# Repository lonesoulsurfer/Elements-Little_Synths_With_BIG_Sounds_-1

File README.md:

# Elements: Little Synths With BIG Sounds #1

Elements is a small analogue synth. It has a pulse-width-modulated (PWM) oscillator and a resonant low-pass filter. It is number 1 in my "Little synths with BIG sounds" series.

## Build guide and video

- Step-by-step build guide on Instructables: [Elements - Little Synths With Big Sounds #1](https://www.instructables.com/Elements-Little-Synths-With-Big-Sounds-1/)
- Video on YouTube: [Elements](https://www.youtube.com/watch?v=f492427Ovs0)

## Features

- PWM oscillator with a "growling" sound, through a resonant low-pass filter
- Control the sound with 2 light-dependent resistors (LDRs), or with LEDs through 2 vactrols
- Knobs for cutoff, speed, modulation and resonance
- CV and gate outputs, to connect a sequencer or other synths
- The front panel is a PCB that fits over the main board
- No case and no complex power supply, to keep the build easy

## What you need

- All parts are in the parts list ([PDF](Parts%20List/Elements%20-%20Parts%20List%20-%20Excel.pdf) or Excel).
- The schematic is [schematic.png](schematic.png).
- The Gerber files for the PCB and the front panel are in [Gerber Files](Gerber%20Files/). You can send them to a PCB maker.

## Build it

The Instructables guide shows each step, with photos. In short:

1. Send the Gerber files to a PCB maker.
2. Get the parts in the parts list.
3. Solder the parts to the PCB.
4. Attach the front panel PCB.
5. Connect the power and test the synth.

## Files in this repository

| Folder or file | Contents |
|----------------|----------|
| `Eagle Files/` | Eagle files for the PCB |
| `Gerber Files/` | Gerber files for the PCB and the front panel, ready to order |
| `Parts List/` | Parts list (PDF and Excel) |
| `schematic.png` | Schematic |

## Support

Do you like this project? You can support my work on [GitHub Sponsors](https://github.com/sponsors/lonesoulsurfer).

## Licence

This project uses the [CERN Open Hardware Licence v2, Strongly Reciprocal](LICENSE) (CERN-OHL-S-2.0). Copyright (c) 2025 Marcus (lonesoulsurfer).

You can make, change and sell boards from these files. If you share or sell a changed design, you must also share the changed design files under the same licence.

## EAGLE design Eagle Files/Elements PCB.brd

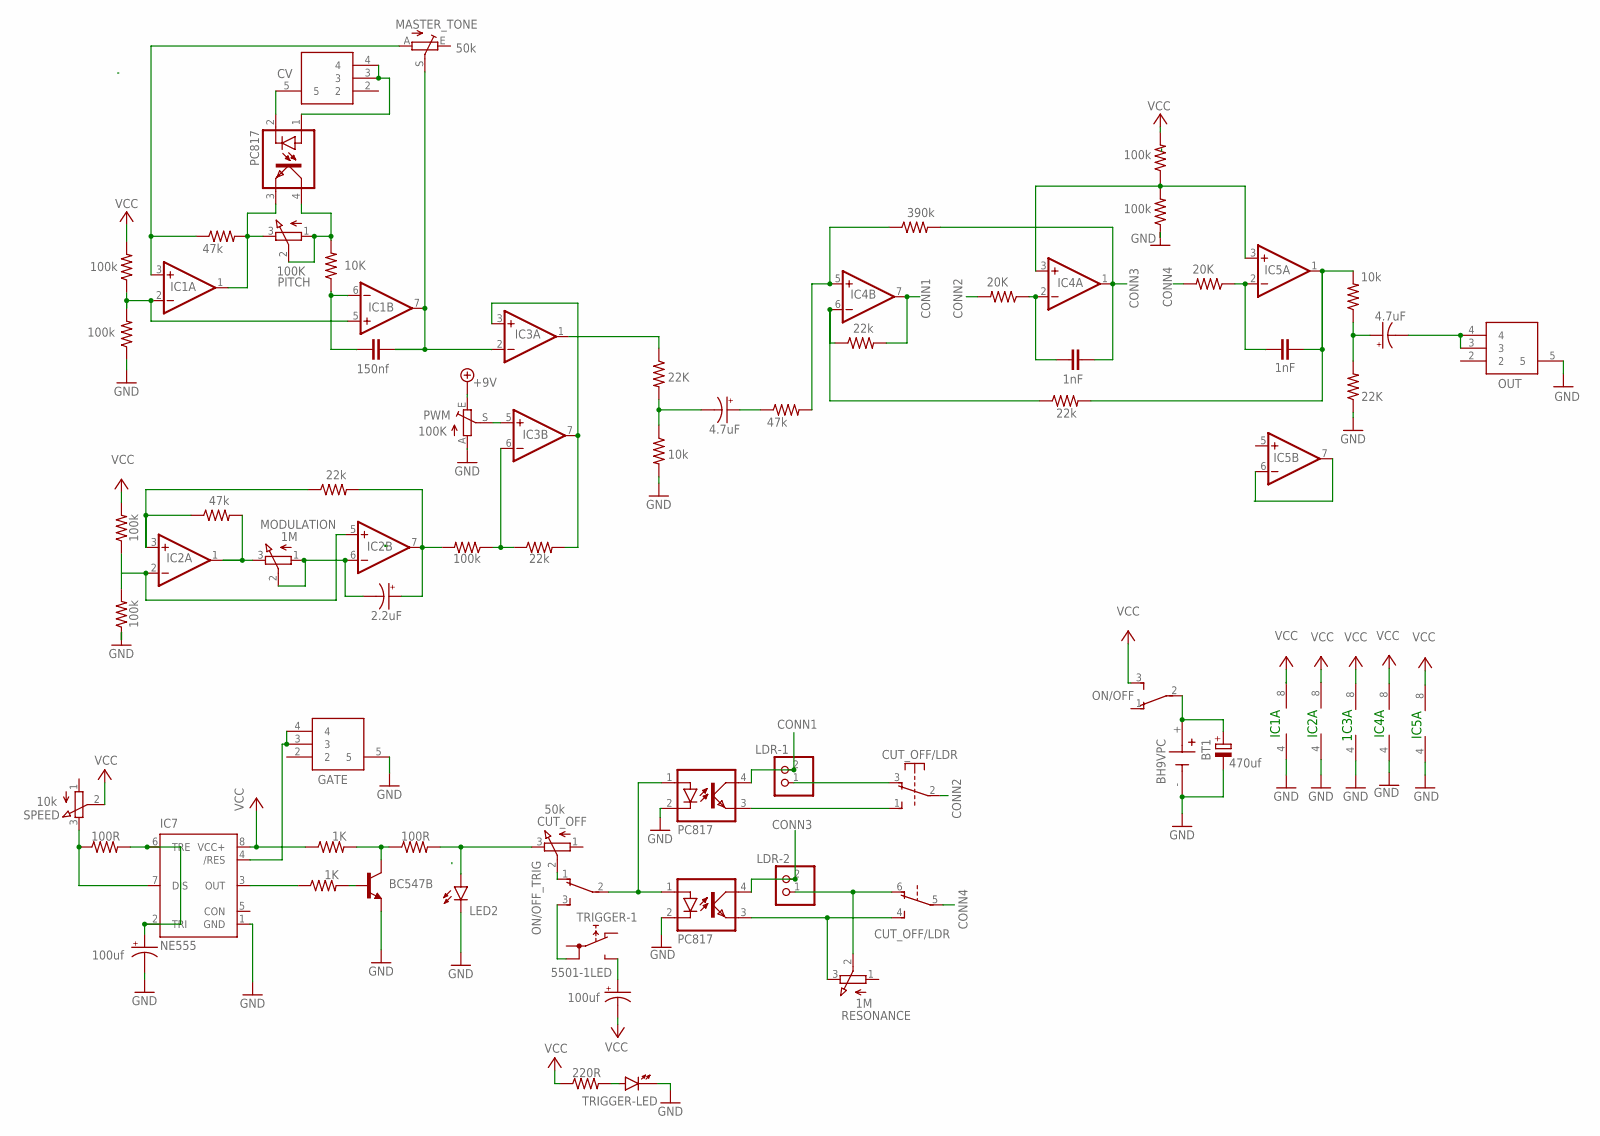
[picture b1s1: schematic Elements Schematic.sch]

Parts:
BT1: BH9VPC; BAT_BH9VPC
C1: 150nf; C050-024X044
C2: 2.2uF; E2,5-5
C3, C6: 4.7uF; E2,5-5
C4, C5: 1nF; C050-024X044
C7, C11: 100uf; E2,5-5
C8: 470uf; E3,5-8
CUT_OFF: 50k; EVUF
CUT_OFF/LDR: SWITCH-6PIN
CV: PJ-320A; PJ320A
GATE: PJ-320A; PJ320A
IC1, IC2, IC3, IC4, IC5: LM358N; DIL08
IC7: NE555; DIL-08
LDR-1, LDR-2: PINHD-1X2; 1X02
LED2: LED3MM
MASTER_TONE: 50k; B25P
MODULATION: 1M; EVUF
OK1, OK2, OK3: PC817; DIL04
ON/OFF: TL36PO; TL3XPO
ON/OFF_TRIG: TL36PO; TL3XPO
OUT: PJ-320A; PJ320A
PITCH: 100K; EVUF
PWM: 100K; B25P
Q1: BC547B; TO92
R1, R2, R3, R4, R7, R15, R19: 100k; 0207/10
R5, R12, R16: 47k; 0207/10
R6, R20: 20K; 0207/10
R8, R13, R18, R21: 22k; 0207/10
R9, R10: 10k; 0207/10
R11, R17: 22K; 0207/10
R14: 390k; 0207/10
R22: 10K; 0207/10
R23: 220R; 0207/10
R38, R40: 100R; 0207/10
R39, R41: 1K; 0207/10
RESONANCE: 1M; EVUF
SPEED: 10k; EVUF
TRIGGER: 5501-1LED

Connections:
CONN1: IC4.7 (OUT), LDR-1.2, OK1.4 (COL), R13.2
CONN2: CUT_OFF/LDR.2, R6.2
CONN3: C4.2, IC4.1 (OUT), LDR-2.2, OK3.4 (COL), R14.2
CONN4: CUT_OFF/LDR.5, R20.2
GND: BT1.-, C8.-, C11.-, GATE.5, IC1.4 (V-), IC2.4 (V-), IC3.4 (V-), IC4.4 (V-), IC5.4 (V-), IC7.1 (GND), LED2.K (C), OK1.2 (C), OK3.2 (C), OUT.5, PWM.A, Q1.1 (E), R2.1, R3.1, R10.2, R17.1, R19.1, TRIGGER.- (K)
unnamed: IC1.3 (+IN), MASTER_TONE.A, R5.1
unnamed: C1.1, IC1.6 (-IN), R22.1
unnamed: IC1.2 (-IN), IC1.5 (+IN), R1.1, R2.2
unnamed: C1.2, IC1.7 (OUT), IC3.2 (-IN), MASTER_TONE.S
unnamed: CUT_OFF.2 (S), ON/OFF_TRIG.1 (O)
unnamed: IC2.2 (-IN), IC2.5 (+IN), R3.2, R4.1
unnamed: IC2.3 (+IN), R16.1, R18.1
unnamed: IC2.1 (OUT), MODULATION.3 (E), R16.2
unnamed: C2.-, IC2.6 (-IN), MODULATION.1 (A), MODULATION.2 (S)
unnamed: C2.+, IC2.7 (OUT), R7.2, R18.2
unnamed: IC3.6 (-IN), R7.1, R8.1
unnamed: IC3.3 (+IN), IC3.7 (OUT), R8.2
unnamed: IC3.5 (+IN), PWM.S
unnamed: IC3.1 (OUT), R11.1
unnamed: C6.+, R9.1, R17.2
unnamed: C3.+, R12.1
unnamed: IC4.5 (+IN), R12.2, R14.1
unnamed: IC4.6 (-IN), R13.1, R21.1
unnamed: C6.-, OUT.3, OUT.4
unnamed: C5.2, IC5.1 (OUT), R9.2, R21.2
unnamed: C4.1, IC4.2 (-IN), R6.1
unnamed: IC4.3 (+IN), IC5.3 (+IN), R15.1, R19.2
unnamed: C3.-, R10.1, R11.2
unnamed: C5.1, IC5.2 (-IN), R20.1
unnamed: OK2.4 (COL), PITCH.1 (A), PITCH.2 (S), R22.2
unnamed: IC5.6 (-IN), IC5.7 (OUT)
unnamed: CV.5, OK2.2 (C)
unnamed: CV.3, CV.4, OK2.1 (A)
unnamed: ON/OFF_TRIG.3 (S), TRIGGER.1B
unnamed: C7.+, TRIGGER.NO
unnamed: R23.2, TRIGGER.+ (A)
unnamed: OK1.1 (A), OK3.1 (A), ON/OFF_TRIG.2
unnamed: GATE.3, GATE.4, IC7.4 (/RES)
unnamed: BT1.+, C8.+, ON/OFF.2
unnamed: IC1.1 (OUT), OK2.3 (EMIT), PITCH.3 (E), R5.2
unnamed: CUT_OFF.3 (E), LED2.A, R40.2
unnamed: CUT_OFF/LDR.3 (O), LDR-1.1
unnamed: CUT_OFF/LDR.1 (S), OK1.3 (EMIT)
unnamed: CUT_OFF/LDR.6 (O), LDR-2.1, RESONANCE.2 (S)
unnamed: CUT_OFF/LDR.4 (S), OK3.3 (EMIT), RESONANCE.3 (E)
unnamed: C11.+, IC7.2 (TRI), IC7.6 (TRE), R38.2
unnamed: IC7.7 (DIS), R38.1, SPEED.3 (E)
unnamed: Q1.3 (C), R40.1, R41.2
unnamed: IC7.3 (OUT), R39.1
unnamed: Q1.2 (B), R39.2
VCC: C7.-, IC1.8 (V+), IC2.8 (V+), IC3.8 (V+), IC4.8 (V+), IC5.8 (V+), IC7.8 (VCC+), ON/OFF.3 (S), PWM.E, R1.2, R4.2, R15.2, R23.1, R41.1, SPEED.2 (S)

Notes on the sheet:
IC1A
1C3A
IC2A
IC4A
IC5A

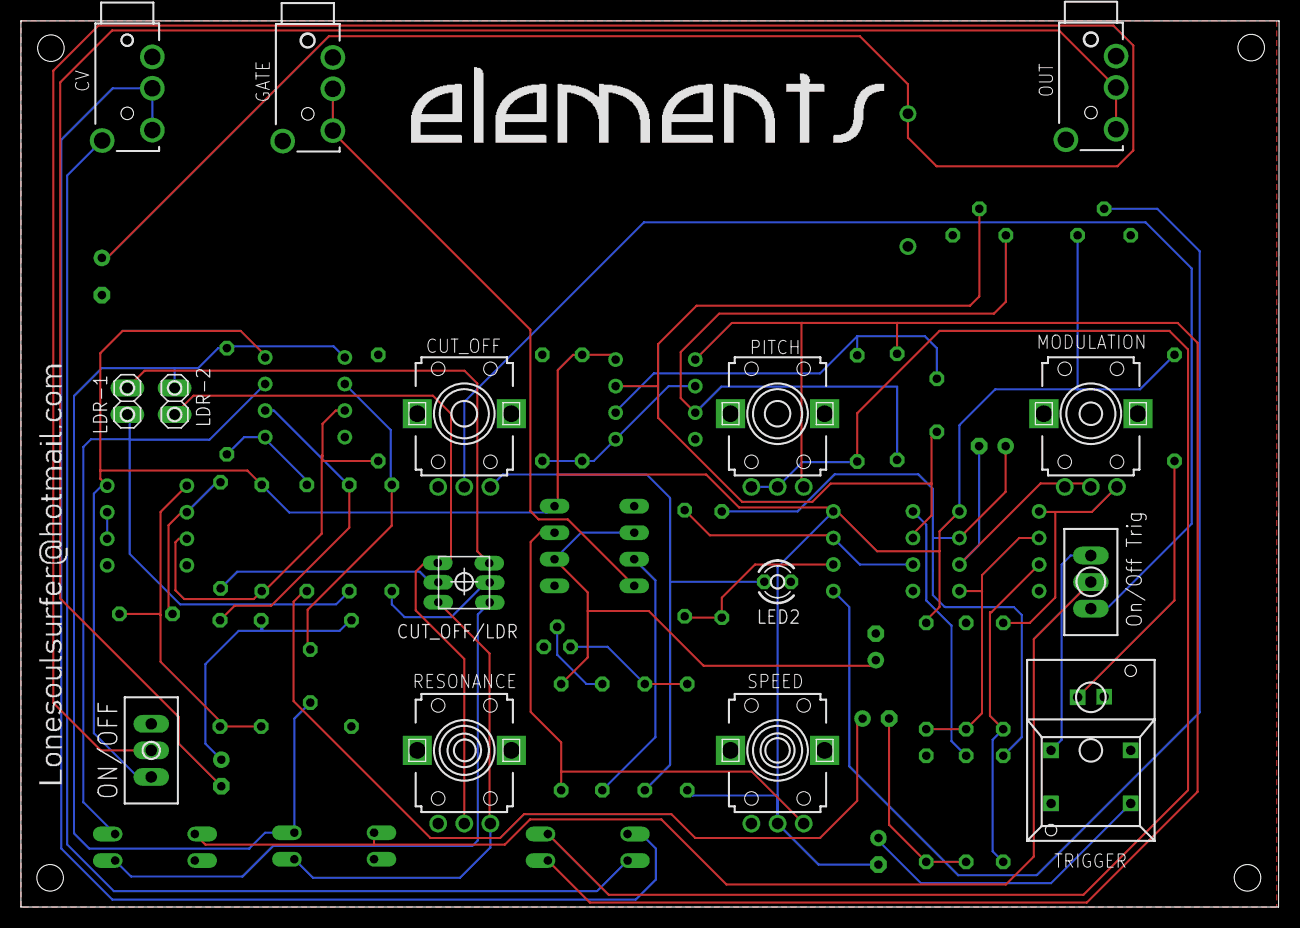
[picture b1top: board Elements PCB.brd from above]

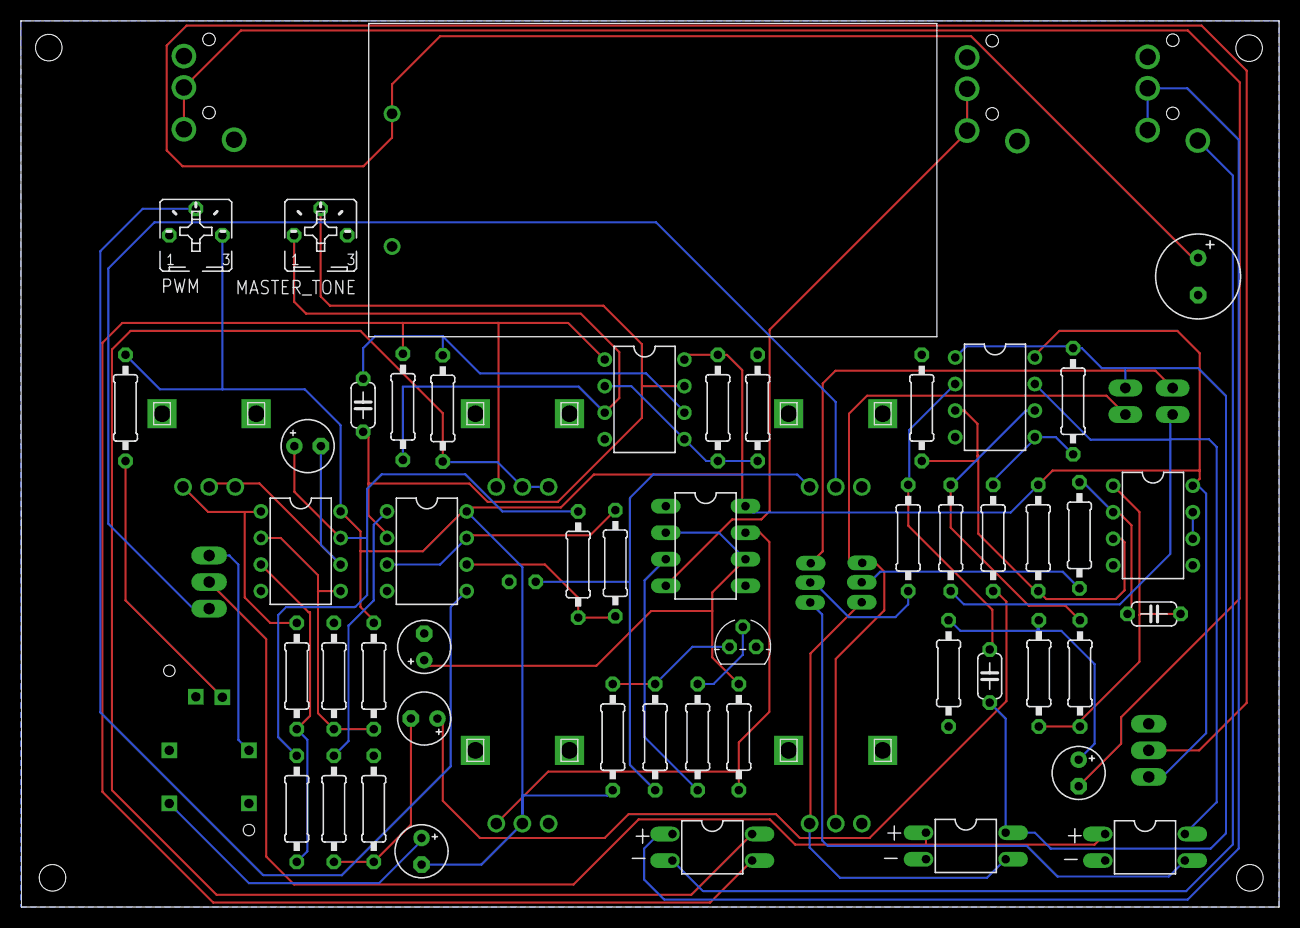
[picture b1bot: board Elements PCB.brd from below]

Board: 2 copper layers, 120.4 x 84.8 mm, 64 parts (49 on the bottom side), 51 nets.
